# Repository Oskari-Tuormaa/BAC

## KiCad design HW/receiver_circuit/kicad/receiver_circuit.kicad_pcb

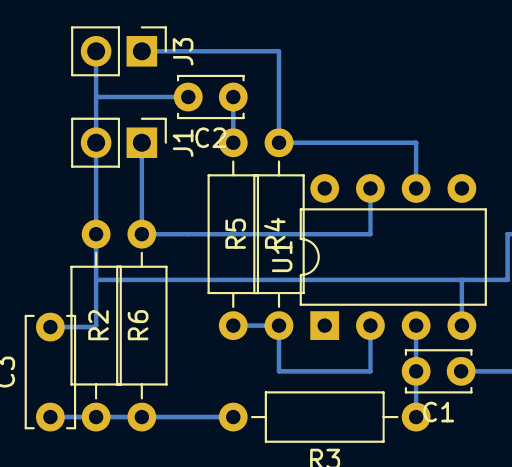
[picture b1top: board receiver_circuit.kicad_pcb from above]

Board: 2 copper layers, 11 parts (0 on the bottom side), 7 nets.

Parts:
C1: 2.69n; C_Disc_D3.4mm_W2.1mm_P2.50mm
C2: 2.65n; C_Disc_D3.4mm_W2.1mm_P2.50mm
C3: 10u; C_Disc_D6.0mm_W2.5mm_P5.00mm
J1: PWR; PinHeader_1x02_P2.54mm_Vertical
J3: OUT; PinHeader_1x02_P2.54mm_Vertical
R2, R3, R5, R6: 100k; R_Axial_DIN0207_L6.3mm_D2.5mm_P10.16mm_Horizontal
R4: 1.5k; R_Axial_DIN0207_L6.3mm_D2.5mm_P10.16mm_Horizontal
U1: MCP601-xP; DIP-8_W7.62mm

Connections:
+3V3: J1.1, R2.2, U1.7 (V+)
Earth: C2.2, C3.2, J1.2, J3.2, R6.1, U1.4 (V-)
unnamed: C1.2, R3.1, U1.3 (+)
unnamed: C2.1, R4.1
unnamed: C3.1, R2.1, R3.2, R6.2
unnamed: R4.2, R5.1, U1.2 (-)
Vout: J3.1, R5.2, U1.6

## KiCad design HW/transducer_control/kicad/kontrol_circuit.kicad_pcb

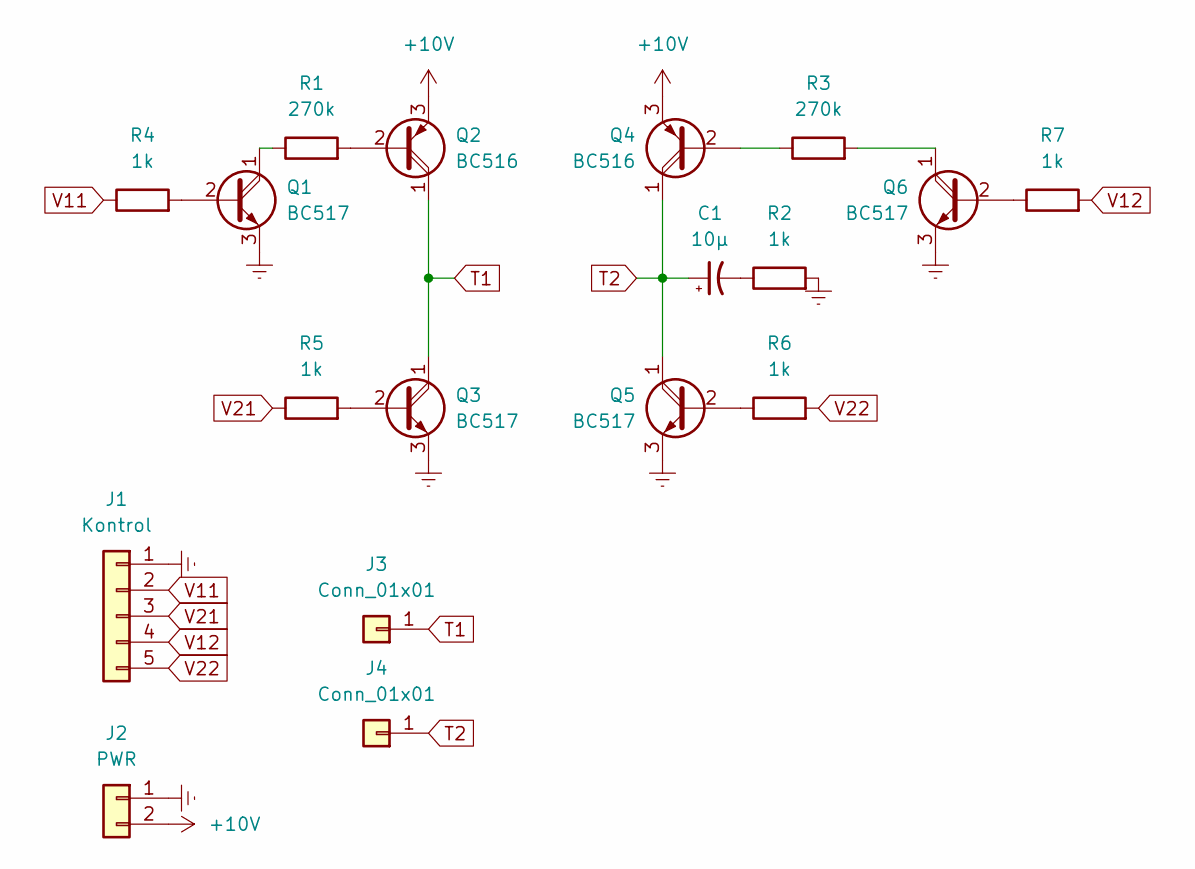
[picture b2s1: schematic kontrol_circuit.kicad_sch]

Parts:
C1: 10μ; CP_Radial_D5.0mm_P2.50mm
J1: Kontrol; PinHeader_1x05_P2.54mm_Vertical
J2: PWR; PinHeader_1x02_P2.54mm_Vertical
J3, J4: Conn_01x01; PinHeader_1x01_P2.54mm_Vertical
Q1, Q3, Q5, Q6: BC517; TO-92_Inline_Wide
Q2, Q4: BC516; TO-92_Inline_Wide
R1, R3: 270k; R_Axial_DIN0204_L3.6mm_D1.6mm_P2.54mm_Vertical
R2, R4, R5, R6, R7: 1k; R_Axial_DIN0207_L6.3mm_D2.5mm_P10.16mm_Horizontal

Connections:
+10V: J2.2, Q2.3 (E), Q4.3 (E)
Earth: J1.1, J2.1, Q1.3 (E), Q3.3 (E), Q5.3 (E), Q6.3 (E), R2.2
unnamed: C1.2, R2.1
unnamed: Q1.1 (C), R1.1
unnamed: Q1.2 (B), R4.2
unnamed: Q2.2 (B), R1.2
unnamed: Q3.2 (B), R5.2
unnamed: Q4.2 (B), R3.1
unnamed: Q5.2 (B), R6.1
unnamed: Q6.1 (C), R3.2
unnamed: Q6.2 (B), R7.1
T1: J3.1, Q2.1 (C), Q3.1 (C)
T2: C1.1, J4.1, Q4.1 (C), Q5.1 (C)
V11: J1.2, R4.1
V12: J1.4, R7.2
V21: J1.3, R5.1
V22: J1.5, R6.2

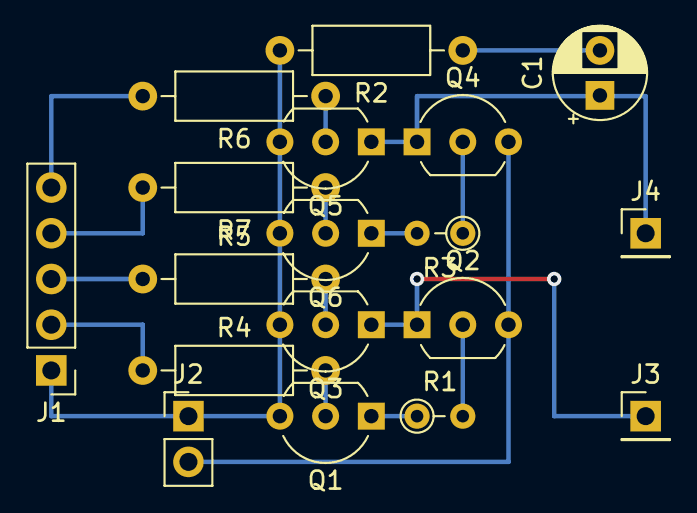
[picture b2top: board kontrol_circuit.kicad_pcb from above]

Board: 2 copper layers, 18 parts (0 on the bottom side), 17 nets.

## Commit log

2022-02-18 Added notebook for linearity calculations
2022-02-20 Removed .ipynb_checkpoints
2022-02-21 Simulated conversion and plots as pdf
2022-02-21 Worked on linearity
2022-03-15 Made subdirectory for jupyter simulations
2022-03-15 Added falstad simulation file for push-pull controller
2022-04-04 Add .idea to gitignore
2022-04-04 Ran some tests
2022-04-07 Added notebook for controlling AD2
2022-04-07 Worked on linearity notebooks
2022-04-09 Add esp_driver_dev project
2022-04-10 Add function comments to pulser component
2022-04-11 Work on ESP32 driver
    Added interrupt routine for sending pulse
    Expanded pulse to full APESW
    Added cross-conduction prevention to driver
2022-04-13 Remove redundant file
2022-04-13 Very small changes to esp_driver_dev
2022-04-13 Added kontrol_circuit KiCAD project
2022-04-13 Add transducer_characteristics jupyter project
2022-04-13 Add esp_control jupyter project
2022-04-13 Changed some plots
2022-04-15 Added receiver_circuit LTSpice sim
2022-04-20 Added ltspice dir
2022-04-21 Added paramsweep data
2022-04-21 Added sweep files
2022-04-21 Changes to receiver circuit ltspice
2022-06-21 Esp driver at time of submission
2022-07-03 Finished BAC
